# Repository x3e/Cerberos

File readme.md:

# Cerberos

## Issue
The screen is not working when powered from USB. In theory the internal CH552 voltage regulator should be able to provide enough current, and with a previous batch of screens, this was working. If you find the issue, please let us know by opening an issue or submitting a pull request.

## Compilation
To compile the software for this project, follow the instructions in the [ch55xduino](https://github.com/DeqingSun/ch55xduino) repository to set up your development environment. Use the following settings after selecting the CH552 board in Arduino:
 - Bootloader pin: P3.6 (D+) pull-up
 - Clock Source: 12 MHz (internal)
 - Upload method: USB
 - USB Settings: User Code w/ 0B USB ram

## License
This project is licensed under the Unlicense License. See the [LICENSE](LICENSE) file for details.

## Contact
If you have any questions or suggestions, feel free to open an issue.

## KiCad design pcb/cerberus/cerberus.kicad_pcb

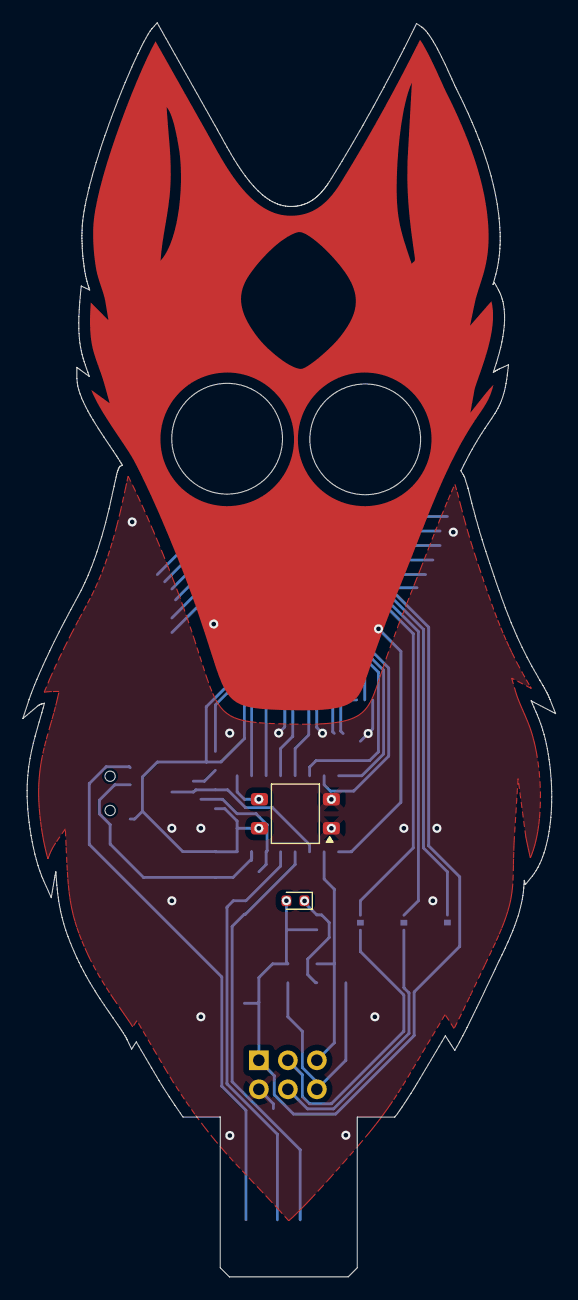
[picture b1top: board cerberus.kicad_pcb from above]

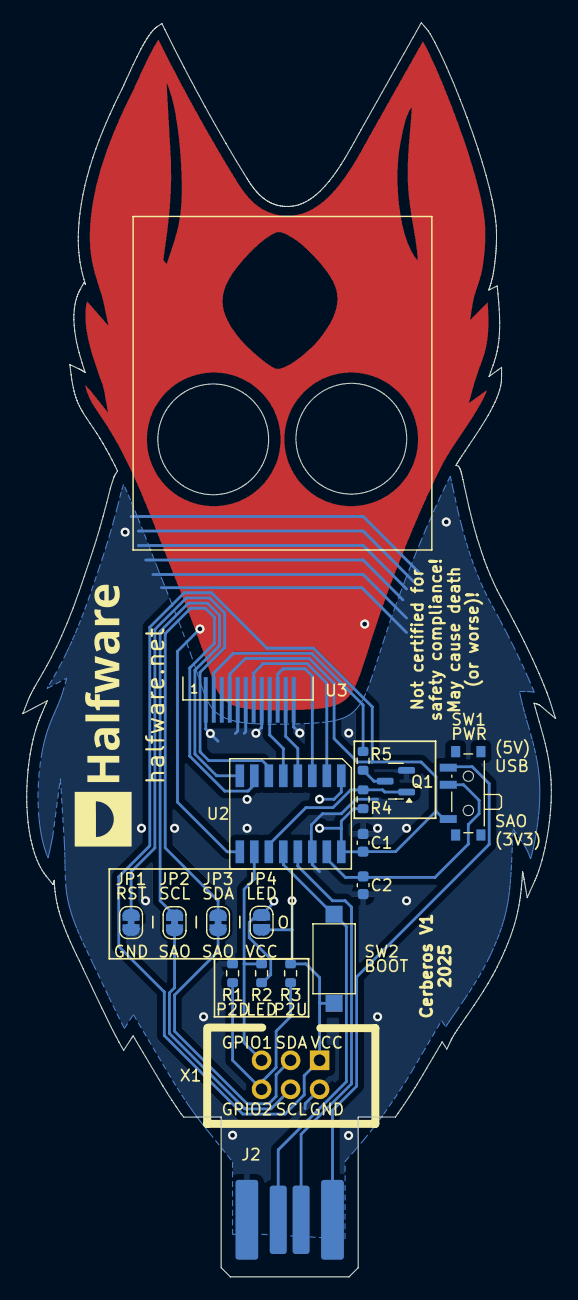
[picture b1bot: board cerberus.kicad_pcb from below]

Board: 2 copper layers, 46.6 x 109.8 mm, 20 parts (17 on the bottom side), 22 nets.

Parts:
C1, C2: 100nF; C_0603_1608Metric
D1: LED; LED_0603_1608Metric
J2: USB_A_PCB_Edge_receptacle
JP1, JP2, JP3: SolderJumper_2_Bridged; SolderJumper-2_P1.3mm_Bridged_RoundedPad1.0x1.5mm
JP4: SolderJumper_2_Open; SolderJumper-2_P1.3mm_Open_RoundedPad1.0x1.5mm
Q1: Q_NMOS_GSD; SOT-23
R1: DNP; R_0603_1608Metric
R2, R4, R5: R; R_0603_1608Metric
R3: 1k; R_0603_1608Metric
SW1: SW_SPDT; SW_SPDT_PCM12
SW2: SW_Push; SW_SPST_CK_RS282G05A3
U1: IRM-H6xxT; Everlight_IRM-H6xxT
U2: CH552G
U3: STP240240-0130A
X1: Simple_Addon_v2; Simple_Addon_v2-SAO-2x3

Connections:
+3V3: C1.1, D1.2 (A), JP4.2 (B), R3.1, R4.1, SW1.1 (A), SW2.2, U1.4 (Vcc), U2.16 (3V3), U3.P3 (LEDA), U3.P4 (VDD), X1.1 (VCC)
+5V: J2.1 (VBUS), SW1.3 (C)
/BACKLIGHT: Q1.1 (G), R4.2, U2.11 (P3.4)
/I2C_SCL: JP2.2 (B), X1.4 (SCL)
/I2C_SDA: JP3.2 (B), X1.3 (SDA)
/IR/SAO_P1: R2.1, U2.10 (P3.3), X1.5 (GPIO1)
/SPI_DC: U2.2 (P1.4), U3.P7 (D/C)
/SPI_RST: U2.4 (P1.6), U3.P11 (RST)
/SPI_SCL: U2.5 (P1.7), U3.P9 (SCL)
/SPI_SDA: U2.3 (P1.5), U3.P10 (SDA)
GND: C1.2, C2.2, J2.4 (GND), JP1.1 (A), Q1.2 (S), R1.2, U1.1 (GND), U1.2 (GND), U2.14 (GND), U3.P1 (GND), U3.P5 (GND), U3.P6 (GND), U3.P8 (CS), U3.P12 (GND), X1.2 (GND)
unnamed: D1.1 (K), JP4.1 (A), R2.2
unnamed: J2.3 (D+), SW2.1, U2.12 (P3.6)
unnamed: J2.2 (D-), U2.13 (P3.7)
unnamed: JP1.2 (B), U2.6 (RST)
unnamed: JP2.1 (A), U2.8 (P3.0)
unnamed: JP3.1 (A), U2.7 (P3.1)
unnamed: Q1.3 (D), R5.2
unnamed: C2.1, SW1.2 (B), U2.15 (VCC)
unnamed: U1.3 (OUT), U2.1 (P3.2)
unnamed: R5.1, U3.P2 (LEDK)
unnamed: R1.1, R3.2, X1.6 (GPIO2)

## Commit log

2025-03-14 Add schematics PDF
2025-03-14 add readme
